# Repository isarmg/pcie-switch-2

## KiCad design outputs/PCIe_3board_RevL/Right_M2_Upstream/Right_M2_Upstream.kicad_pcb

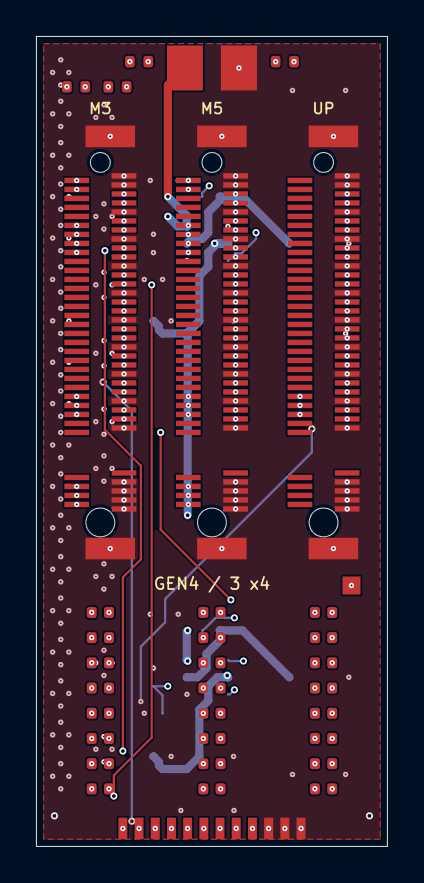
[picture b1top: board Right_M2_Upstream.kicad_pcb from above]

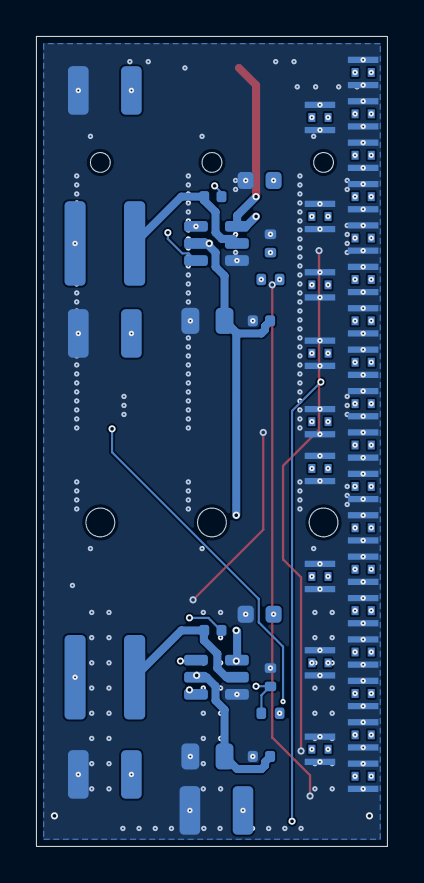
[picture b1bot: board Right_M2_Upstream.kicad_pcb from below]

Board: 32 copper layers, 19.5 x 45.0 mm, 81 parts (47 on the bottom side), 97 nets.

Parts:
C301, C501: 10uF 25V X7R; C_0805_2012Metric
C302, C502: 100nF 50V; C_0402_1005Metric
C303, C503: 100nF 25V; C_0402_1005Metric
C304, C305, C504, C505: 22uF 16V X7R; C_1210_3225Metric
C306, C506: 1uF 16V; C_0603_1608Metric
C320, C321, C322, C323, C324, C325, C326, C327, C420, C421, C422, C423, C424, C425, C426, C427, C520, C521, C522, C523, C524, C525, C526, C527: 220nF 16V AC; C_0402_1005Metric
J3: M3 SSD / MDT350M01001VT Gen4; Amphenol_MDT350M01001VT_MKey_Vertical_Gen4
J4: HOST UPSTREAM / MDT350M01001VT Gen4; Amphenol_MDT350M01001VT_MKey_Vertical_Gen4
J5: M5 SSD / MDT350M01001VT Gen4; Amphenol_MDT350M01001VT_MKey_Vertical_Gen4
J50: 12V protected / GND; Wire_12V_GND_3A
J51: Three x4 port control / 12-wire; Control_12_Wire
J101: M3 TX0; Twinax_85R_Solder_DRAFT
J102: M3 RX0; Twinax_85R_Solder_DRAFT
J103: M3 TX1; Twinax_85R_Solder_DRAFT
J104: M3 RX1; Twinax_85R_Solder_DRAFT
J105: M3 TX2; Twinax_85R_Solder_DRAFT
J106: M3 RX2; Twinax_85R_Solder_DRAFT
J107: M3 TX3; Twinax_85R_Solder_DRAFT
J108: M3 RX3; Twinax_85R_Solder_DRAFT
J109: M3 CLK; Twinax_85R_Solder_DRAFT
J110: UP TX0; Twinax_85R_Solder_DRAFT
J111: UP RX0; Twinax_85R_Solder_DRAFT
J112: UP TX1; Twinax_85R_Solder_DRAFT
J113: UP RX1; Twinax_85R_Solder_DRAFT
J114: UP TX2; Twinax_85R_Solder_DRAFT
J115: UP RX2; Twinax_85R_Solder_DRAFT
J116: UP TX3; Twinax_85R_Solder_DRAFT
J117: UP RX3; Twinax_85R_Solder_DRAFT
J118: UP CLK; Twinax_85R_Solder_DRAFT
J119: M5 TX0; Twinax_85R_Solder_DRAFT
J120: M5 RX0; Twinax_85R_Solder_DRAFT
J121: M5 TX1; Twinax_85R_Solder_DRAFT
J122: M5 RX1; Twinax_85R_Solder_DRAFT
J123: M5 TX2; Twinax_85R_Solder_DRAFT
J124: M5 RX2; Twinax_85R_Solder_DRAFT
J125: M5 TX3; Twinax_85R_Solder_DRAFT
J126: M5 RX3; Twinax_85R_Solder_DRAFT
J127: M5 CLK; Twinax_85R_Solder_DRAFT
L3, L5: 2.2uH XAL5030-222MEC; L_Coilcraft_XAL5030-XXX
R301, R501: 33.2k; R_0402_1005Metric
R302, R310, R311, R502, R510, R511: 10k; R_0402_1005Metric
TP1: UP CLKREQ reserved; Testpad_1
U23, U25: TPS565201DDCR; SOT-23-6

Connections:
/CABLE12: C301.1, C302.1, C501.1, C502.1, J50.1, U23.3, U23.5, U25.3, U25.5
/GND: C301.2, C302.2, C304.2, C305.2, C306.2, C501.2, C502.2, C504.2, C505.2, C506.2, J3.1, J3.3, J3.9, J3.15, J3.21, J3.27, J3.33, J3.39, J3.45, J3.51, J3.57, J3.69, J3.71, J3.73, J3.75, J3.MP1, J3.MP2, J4.1, J4.3, J4.9, J4.15, J4.21, J4.27, J4.33, J4.39, J4.45, J4.51, J4.57, J4.69, J4.71, J4.73, J4.75, J4.MP1, J4.MP2, J5.1, J5.3, J5.9, J5.15, J5.21, J5.27, J5.33, J5.39, J5.45, J5.51, J5.57, J5.69, J5.71, J5.73, J5.75, J5.MP1, J5.MP2, J50.2, J51.10, J51.11, J51.12, J101.G, J102.G, J103.G, J104.G, J105.G, J106.G, J107.G, J108.G, J109.G, J110.G, J111.G, J112.G, J113.G, J114.G, J115.G, J116.G, J117.G, J118.G, J119.G, J120.G, J121.G, J122.G, J123.G, J124.G, J125.G, J126.G, J127.G, R302.2, R502.2, U23.1, U25.1
/M3_3V3: C304.1, C305.1, C306.1, J3.2, J3.4, J3.12, J3.14, J3.16, J3.18, J3.70, J3.72, J3.74, L3.2, R301.1, R310.1, R311.1
/M3_BST: C303.1, U23.6
/M3_CLKREQ: J3.52, J51.2, R310.2
/M3_CLK_N: J3.53, J109.N
/M3_CLK_P: J3.55, J109.P
/M3_FB: R301.2, R302.1, U23.4
/M3_PERST: J3.50, J51.1
/M3_RX0_N: J3.41, J102.N
/M3_RX0_P: J3.43, J102.P
/M3_RX1_N: J3.29, J104.N
/M3_RX1_P: J3.31, J104.P
/M3_RX2_N: J3.17, J106.N
/M3_RX2_P: J3.19, J106.P
/M3_RX3_N: J3.5, J108.N
/M3_RX3_P: J3.7, J108.P
/M3_SW: C303.2, L3.1, U23.2
/M3_TX0_N: C321.1, J101.N
/M3_TX0_N_AC: C321.2, J3.47
/M3_TX0_P: C320.1, J101.P
/M3_TX0_P_AC: C320.2, J3.49
/M3_TX1_N: C323.1, J103.N
/M3_TX1_N_AC: C323.2, J3.35
/M3_TX1_P: C322.1, J103.P
/M3_TX1_P_AC: C322.2, J3.37
/M3_TX2_N: C325.1, J105.N
/M3_TX2_N_AC: C325.2, J3.23
/M3_TX2_P: C324.1, J105.P
/M3_TX2_P_AC: C324.2, J3.25
/M3_TX3_N: C327.1, J107.N
/M3_TX3_N_AC: C327.2, J3.11
/M3_TX3_P: C326.1, J107.P
/M3_TX3_P_AC: C326.2, J3.13
/M3_WAKE: J3.54, J51.3, R311.2
/M5_3V3: C504.1, C505.1, C506.1, J5.2, J5.4, J5.12, J5.14, J5.16, J5.18, J5.70, J5.72, J5.74, L5.2, R501.1, R510.1, R511.1
/M5_BST: C503.1, U25.6
/M5_CLKREQ: J5.52, J51.8, R510.2
/M5_CLK_N: J5.53, J127.N
/M5_CLK_P: J5.55, J127.P
/M5_FB: R501.2, R502.1, U25.4
/M5_PERST: J5.50, J51.7
/M5_RX0_N: J5.41, J120.N
/M5_RX0_P: J5.43, J120.P
/M5_RX1_N: J5.29, J122.N
/M5_RX1_P: J5.31, J122.P
/M5_RX2_N: J5.17, J124.N
/M5_RX2_P: J5.19, J124.P
/M5_RX3_N: J5.5, J126.N
/M5_RX3_P: J5.7, J126.P
/M5_SW: C503.2, L5.1, U25.2
/M5_TX0_N: C521.1, J119.N
/M5_TX0_N_AC: C521.2, J5.47
/M5_TX0_P: C520.1, J119.P
/M5_TX0_P_AC: C520.2, J5.49
/M5_TX1_N: C523.1, J121.N
/M5_TX1_N_AC: C523.2, J5.35
/M5_TX1_P: C522.1, J121.P
/M5_TX1_P_AC: C522.2, J5.37
/M5_TX2_N: C525.1, J123.N
/M5_TX2_N_AC: C525.2, J5.23
/M5_TX2_P: C524.1, J123.P
/M5_TX2_P_AC: C524.2, J5.25
/M5_TX3_N: C527.1, J125.N
/M5_TX3_N_AC: C527.2, J5.11
/M5_TX3_P: C526.1, J125.P
/M5_TX3_P_AC: C526.2, J5.13
/M5_WAKE: J5.54, J51.9, R511.2
/UP_CLKREQ: J4.52, J51.5, TP1.1
/UP_CLK_N: J4.53, J118.N
/UP_CLK_P: J4.55, J118.P
/UP_PERST: J4.50, J51.4
/UP_RX0_N: J4.47, J111.N
/UP_RX0_P: J4.49, J111.P
/UP_RX1_N: J4.35, J113.N
/UP_RX1_P: J4.37, J113.P
/UP_RX2_N: J4.23, J115.N
/UP_RX2_P: J4.25, J115.P
/UP_RX3_N: J4.11, J117.N
/UP_RX3_P: J4.13, J117.P
/UP_TX0_N: C421.1, J110.N
/UP_TX0_N_AC: C421.2, J4.41
/UP_TX0_P: C420.1, J110.P
/UP_TX0_P_AC: C420.2, J4.43
/UP_TX1_N: C423.1, J112.N
/UP_TX1_N_AC: C423.2, J4.29
/UP_TX1_P: C422.1, J112.P
/UP_TX1_P_AC: C422.2, J4.31
/UP_TX2_N: C425.1, J114.N
/UP_TX2_N_AC: C425.2, J4.17
/UP_TX2_P: C424.1, J114.P
/UP_TX2_P_AC: C424.2, J4.19
/UP_TX3_N: C427.1, J116.N
/UP_TX3_N_AC: C427.2, J4.5
/UP_TX3_P: C426.1, J116.P
/UP_TX3_P_AC: C426.2, J4.7
/UP_WAKE: J4.54, J51.6
